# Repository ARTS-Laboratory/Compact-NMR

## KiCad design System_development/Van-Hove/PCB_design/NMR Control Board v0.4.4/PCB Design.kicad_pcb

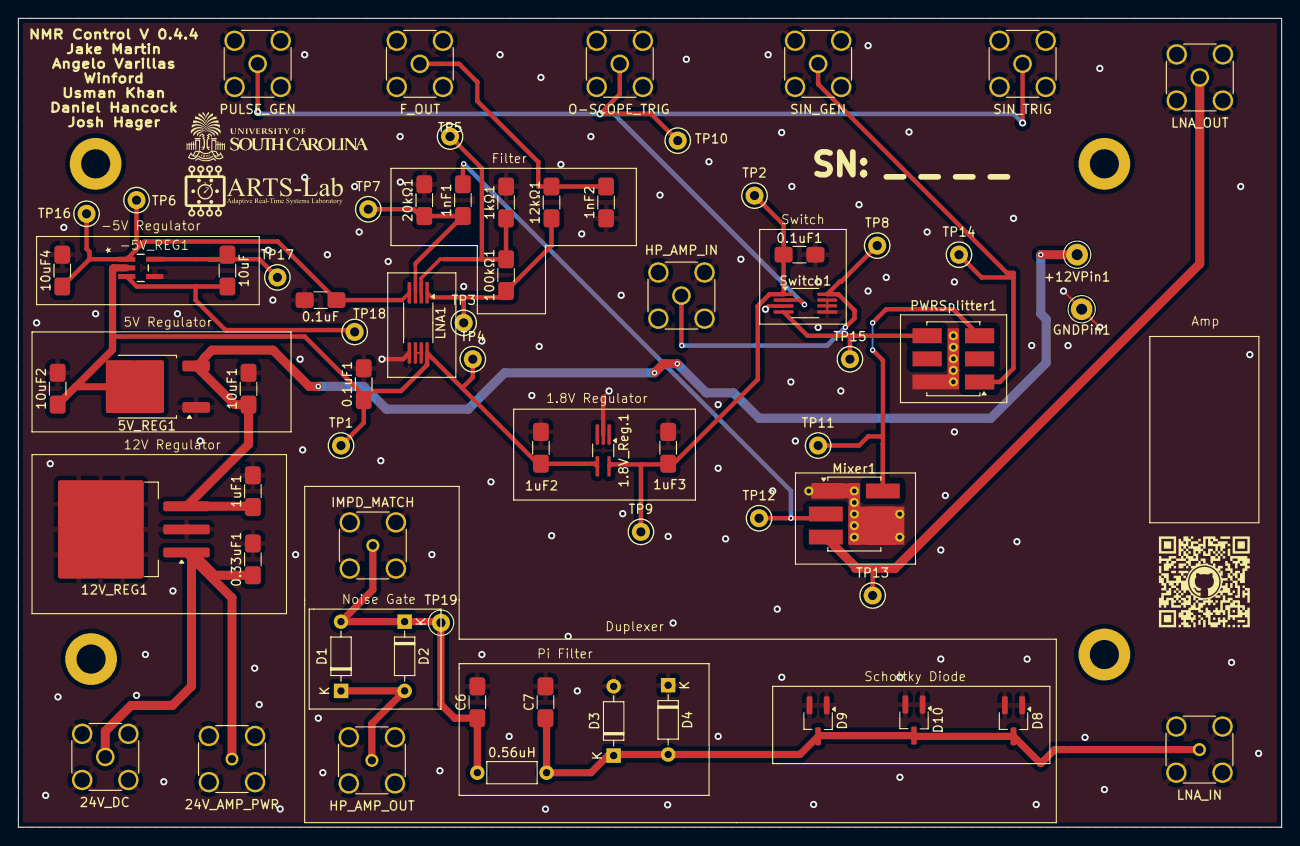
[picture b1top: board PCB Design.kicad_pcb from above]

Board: 2 copper layers, 139.0 x 89.0 mm, 68 parts (0 on the bottom side), 23 nets.

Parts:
0.1uF, 0.1uF1, 0.1uF1#2: 0.1μF; CustomR
0.33uF1: 0.33μF; CustomR
0.56uH: L; L_Axial_L5.3mm_D2.2mm_P7.62mm_Horizontal_Vishay_IM-1
1.8V_Reg.1: NCP715-1.8V; 1.8VReg
1kΩ1: 1kΩ; CustomR
1nF1, 1nF2: 1nF; CustomR
1uF1, 1uF2, 1uF3: 1μF; CustomR
5V_REG1: NCP1117-5.0_TO252; 5VReg2
10uF, 10uF1, 10uF2, 10uF4: 10μF; CustomR
12V_REG1: LM7812_TO220; 5VReg
12kΩ1: 12kΩ; CustomR
20kΩ1: 20kΩ; CustomR
24V_AMP_PWR: 24V Amp; SMA_Amphenol_132134-14_Vertical
24V_DC: 24V DC; SMA_Amphenol_132134_Vertical
100kΩ1: 100kΩ; CustomR
+12VPin1: Conn_Coaxial; Pin_D1.0mm_L10.0mm_LooseFit
-5V_REG1: LM828M5; Mf05A
C6: C14; CustomR
C7: C15; CustomR
D1, D2, D3, D4: 1N4148; D_DO-35_SOD27_P7.62mm_Horizontal
D8, D9, D10: D_Schottky_Dual_Series_AKC; TSOT-23_HandSoldering
F_OUT: Output Function; SMA_Amphenol_132134_Vertical
GNDPin1: Conn_Coaxial; Pin_D1.0mm_L10.0mm_LooseFit
HP_AMP_IN: Sine Out; SMA_Amphenol_132134_Vertical
HP_AMP_OUT: Input 1; SMA_Amphenol_132134-14_Vertical
IMPD_MATCH: Imped Match; SMA_Amphenol_132134-14_Vertical
LNA1: LM4565; LNA
LNA_IN: Output; SMA_Amphenol_132134-14_Vertical
LNA_OUT: Mix RF; SMA_Amphenol_132134_Vertical
Mixer1: ADE-6; Mixer2
O-SCOPE_TRIG: Trig Out; SMA_Amphenol_132134_Vertical
PULSE_GEN: Pulse Wave; SMA_Amphenol_132134_Vertical
PWRSplitter1: ADP-2-1W; Mini-Circuits_CD636_LandPatternPL-035
SIN_GEN: SPI In; SMA_Amphenol_132134_Vertical
SIN_TRIG: Sine Wave; SMA_Amphenol_132134_Vertical
Switch1: ADG901BRMZ; Switch
TP1, TP2, TP3, TP4, TP5, TP6, TP7, TP8, TP9, TP10, TP11, TP12, TP13, TP14, TP15, TP16, TP17, TP18, TP19: TestPoint; TestPoint_Keystone_5000-5004_Miniature

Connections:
GND: 0.1uF.2, 0.1uF1.2, 0.1uF1#2.2, 0.33uF1.2, 1.8V_Reg.1.2 (GND), 1kΩ1.2, 1nF2.1, 1uF1.2, 1uF2.2, 1uF3.2, 5V_REG1.1 (GND), 10uF1.2, 10uF2.2, 10uF4.2, 12V_REG1.2 (GND), 20kΩ1.2, 24V_AMP_PWR.2 (Ext), 24V_DC.2 (Ext), -5V_REG1.4 (GND), C6.2, C7.2, D3.2 (A), D4.1 (K), D8.1 (A), D8.2 (K), D9.1 (A), D9.2 (K), D10.1 (A), D10.2 (K), F_OUT.2 (Ext), GNDPin1.1 (In), HP_AMP_IN.2 (Ext), HP_AMP_OUT.2 (Ext), IMPD_MATCH.2 (Ext), LNA1.5 (+IN2), LNA_IN.2 (Ext), LNA_OUT.2 (Ext), Mixer1.1 (GND), Mixer1.4 (GND), Mixer1.5 (GND), O-SCOPE_TRIG.2 (Ext), PULSE_GEN.2 (Ext), PWRSplitter1.6 (GND), SIN_GEN.2 (Ext), SIN_TRIG.2 (Ext), Switch1.3 (GND), Switch1.5 (GND), Switch1.6 (GND), Switch1.7 (GND)
unnamed: 0.1uF1#2.1, 1.8V_Reg.1.5 (OUT), 1uF3.1, Switch1.1 (VDD), TP2.1, TP9.1
unnamed: 0.33uF1.1, 12V_REG1.1 (VI), 24V_AMP_PWR.1 (In), 24V_DC.1 (In)
unnamed: 1uF1.1, 5V_REG1.3 (VI), 10uF1.1, 12V_REG1.3 (VO), +12VPin1.1 (In)
unnamed: 10uF.1, -5V_REG1.5 (C1+), TP17.1
unnamed: 10uF.2, -5V_REG1.3 (C1-), TP18.1
unnamed: 0.1uF.1, 10uF4.1, -5V_REG1.1 (OUT), LNA1.4 (VEE), TP6.1, TP16.1
unnamed: 0.1uF1.1, 1.8V_Reg.1.4 (IN), 1uF2.1, 5V_REG1.2 (VO), 10uF2.1, -5V_REG1.2 (V+), LNA1.8 (VCC), TP1.1, TP4.1
unnamed: 0.56uH.1, C6.1, D1.2 (A), D2.1 (K), IMPD_MATCH.1 (In), TP19.1
unnamed: D1.1 (K), D2.2 (A), HP_AMP_OUT.1 (In)
unnamed: 0.56uH.2, C7.1, D3.1 (K), D4.2 (A), D8.3 (common), D9.3 (common), D10.3 (common), LNA_IN.1 (In)
unnamed: O-SCOPE_TRIG.1 (In), PULSE_GEN.1 (In), SIN_TRIG.1 (In), Switch1.2 (CTRL), TP10.1
unnamed: HP_AMP_IN.1 (In), Switch1.8 (RF2), TP8.1
unnamed: PWRSplitter1.1 (SUM), SIN_GEN.1 (In), TP14.1
unnamed: LNA_OUT.1 (In), Mixer1.3 (RF), TP13.1
unnamed: 1nF2.2, 12kΩ1.2, F_OUT.1 (In)
unnamed: 1nF1.1, 20kΩ1.1, LNA1.3 (+IN1), TP7.1
unnamed: 1kΩ1.1, 100kΩ1.2, LNA1.2 (-IN1), TP5.1
unnamed: LNA1.6 (-IN2), LNA1.7 (OUT2)
unnamed: 12kΩ1.1, 100kΩ1.1, LNA1.1 (OUT1), TP3.1
unnamed: 1nF1.2, Mixer1.2 (IF), TP12.1
unnamed: Mixer1.6 (LO), PWRSplitter1.3 (PORT1), TP11.1
unnamed: PWRSplitter1.4 (PORT2), Switch1.4 (RF1), TP15.1

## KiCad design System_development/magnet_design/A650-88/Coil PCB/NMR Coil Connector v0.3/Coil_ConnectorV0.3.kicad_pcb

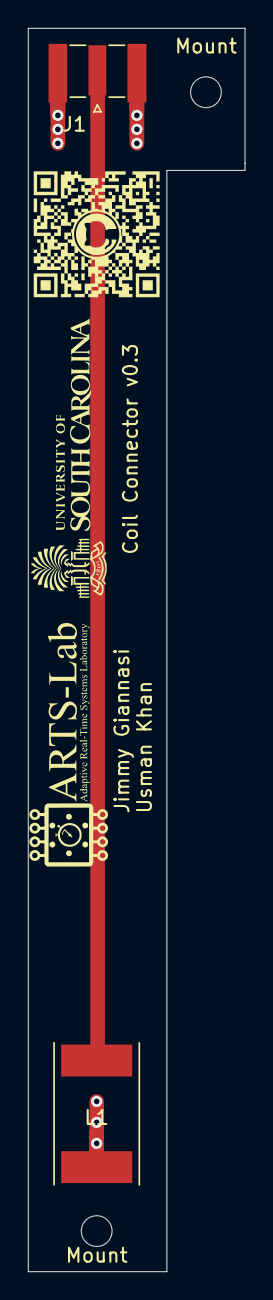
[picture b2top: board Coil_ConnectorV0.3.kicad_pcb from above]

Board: 2 copper layers, 15.5 x 88.9 mm, 4 parts (0 on the bottom side), 2 nets.

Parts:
J1: Conn_Coaxial; SMA_Samtec_SMA-J-P-X-ST-EM1_EdgeMount
L1: L; L_Coil
Mount: MountingHole_2.2mm_M2
Mount#2: MountingHole_2.2mm_M2

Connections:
GND: J1.2, L1.2
unnamed: J1.1, L1.1

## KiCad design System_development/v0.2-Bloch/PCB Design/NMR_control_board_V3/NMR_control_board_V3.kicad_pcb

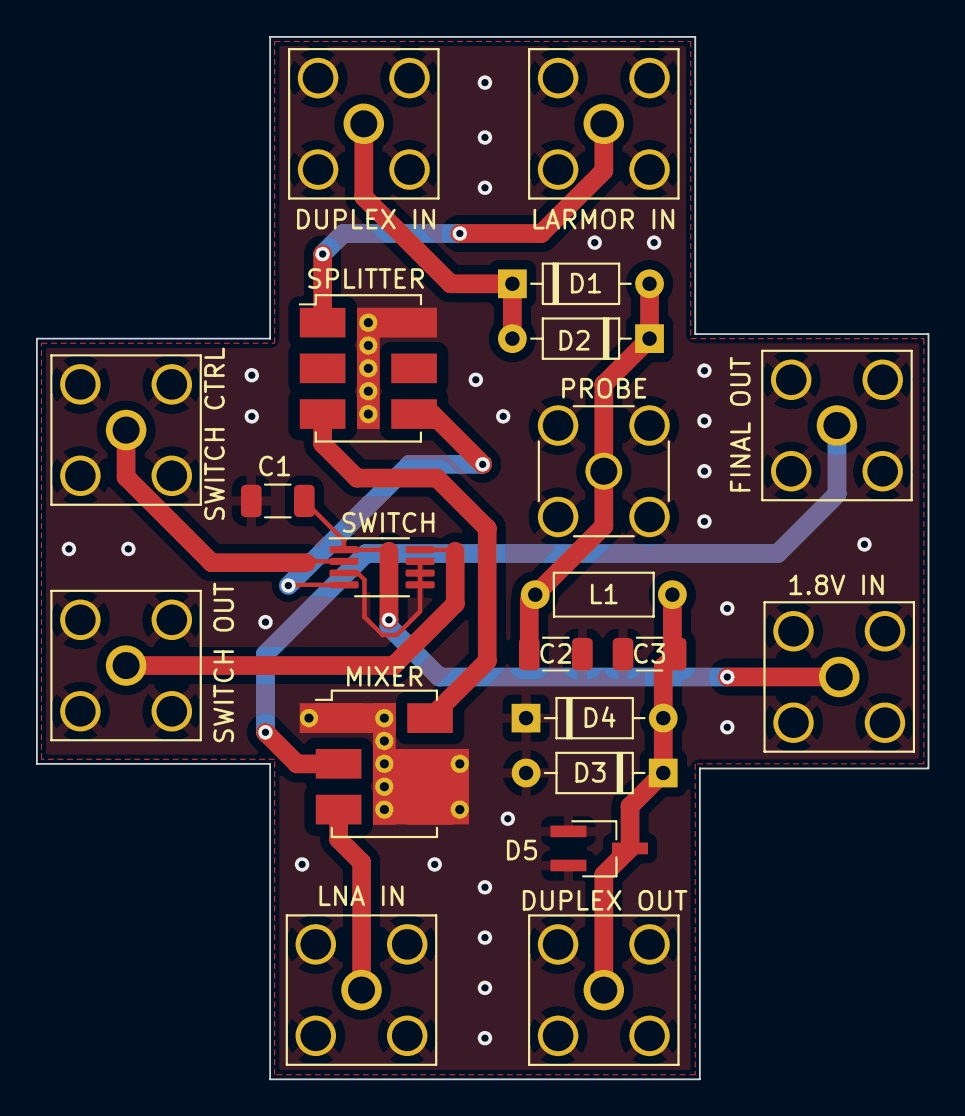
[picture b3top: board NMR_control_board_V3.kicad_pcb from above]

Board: 2 copper layers, 49.5 x 57.9 mm, 21 parts (0 on the bottom side), 12 nets.

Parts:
1.8V IN: Conn_Coaxial; SMA_Amphenol_132203-12_Horizontal
C1: 0.1 uF; C_1206_3216Metric
C2, C3: C; C_1206_3216Metric
D1, D2, D3, D4: 1N4148; D_DO-35_SOD27_P7.62mm_Horizontal
D5: D_Schottky_Dual_Series_AKC; TSOT-23_HandSoldering
DUPLEX IN: Conn_Coaxial; SMA_Amphenol_132203-12_Horizontal
DUPLEX OUT: Conn_Coaxial; SMA_Amphenol_132203-12_Horizontal
FINAL OUT: Conn_Coaxial; SMA_Amphenol_132203-12_Horizontal
L1: INDUCTOR; L_Axial_L5.3mm_D2.2mm_P7.62mm_Horizontal_Vishay_IM-1
LARMOR IN: Conn_Coaxial; SMA_Amphenol_132203-12_Horizontal
LNA IN: Conn_Coaxial; SMA_Amphenol_132203-12_Horizontal
MIXER: ADE-6; Mini-Circuits_CD542_LandPatternPL-052
PROBE: Conn_Coaxial; SMA_Amphenol_132291-12_Vertical
SPLITTER: ADP-2-1W; Mini-Circuits_CD636_LandPatternPL-035
SWITCH: ADG901BRMZ; MSOP-8_3x3mm_P0.65mm
SWITCH CTRL: Conn_Coaxial; SMA_Amphenol_132203-12_Horizontal
SWITCH OUT: Conn_Coaxial; SMA_Amphenol_132203-12_Horizontal

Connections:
GND: 1.8V IN.2 (Ext), C1.1, C2.2, C3.2, D3.2 (A), D4.1 (K), D5.1 (A), D5.2 (K), DUPLEX IN.2 (Ext), DUPLEX OUT.2 (Ext), FINAL OUT.2 (Ext), LARMOR IN.2 (Ext), LNA IN.2 (Ext), MIXER.1 (GND), MIXER.4 (GND), MIXER.5 (GND), PROBE.2 (Ext), SPLITTER.6 (GND), SWITCH.3 (GND), SWITCH.5 (GND), SWITCH.6 (GND), SWITCH.7 (GND), SWITCH CTRL.2 (Ext), SWITCH OUT.2 (Ext)
unnamed: 1.8V IN.1 (In), C1.2, SWITCH.1 (VDD)
unnamed: C2.1, D1.2 (A), D2.1 (K), L1.1, PROBE.1 (In)
unnamed: C3.1, D3.1 (K), D4.2 (A), D5.3 (common), DUPLEX OUT.1 (In), L1.2
unnamed: D1.1 (K), D2.2 (A), DUPLEX IN.1 (In)
unnamed: LARMOR IN.1 (In), SPLITTER.1 (SUM)
unnamed: SWITCH.2 (CTRL), SWITCH CTRL.1 (In)
unnamed: LNA IN.1 (In), MIXER.3 (RF)
unnamed: FINAL OUT.1 (In), MIXER.2 (IF)
unnamed: SWITCH.8 (RF2), SWITCH OUT.1 (In)
unnamed: MIXER.6 (LO), SPLITTER.3 (PORT1)
unnamed: SPLITTER.4 (PORT2), SWITCH.4 (RF1)

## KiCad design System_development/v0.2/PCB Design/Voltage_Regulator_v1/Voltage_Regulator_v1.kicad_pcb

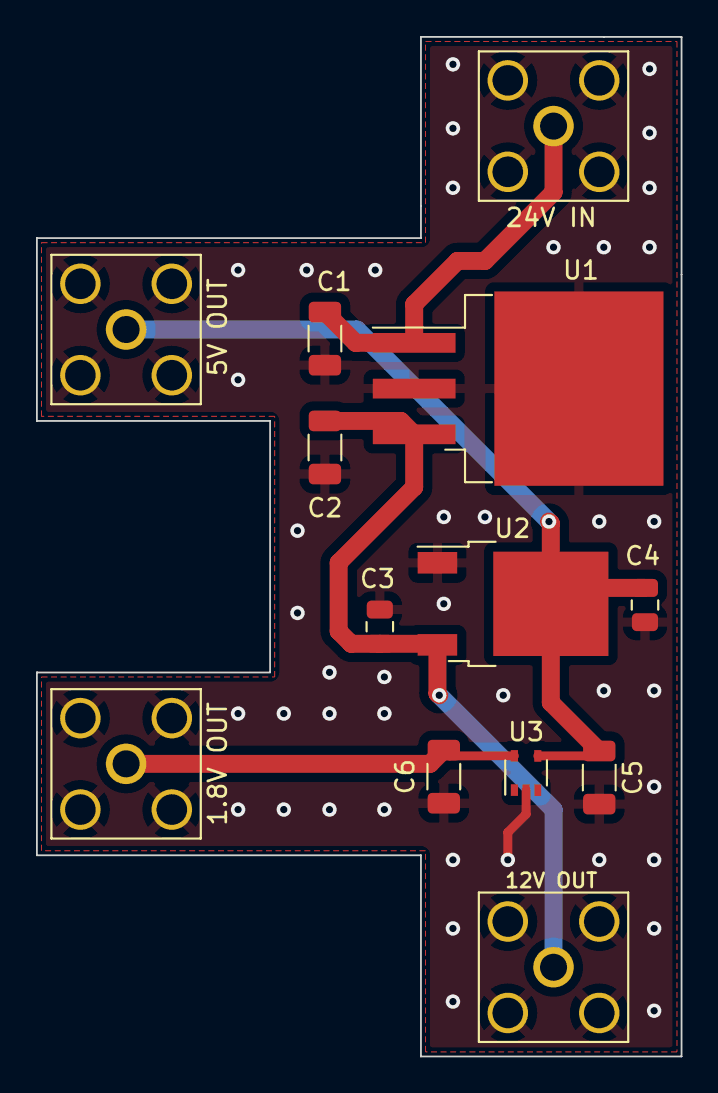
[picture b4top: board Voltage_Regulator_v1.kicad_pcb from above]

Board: 2 copper layers, 35.8 x 56.6 mm, 13 parts (0 on the bottom side), 5 nets.

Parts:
1.8V OUT, 5V OUT, 12V OUT, 24V IN: Conn_Coaxial; SMA_Amphenol_132203-12_Horizontal
C1: 0.33 uF; C_1206_3216Metric
C2, C5, C6: 1 uF; C_1206_3216Metric
C3, C4: 10 uF; C_0805_2012Metric
U1: LM7812_TO220; TO-263-3_TabPin2
U2: NCP1117-5.0_TO252; TO-252-2
U3: NCP715-1.8V; SOT-353_SC-70-5

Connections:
GND: 1.8V OUT.2 (Ext), 5V OUT.2 (Ext), 12V OUT.2 (Ext), 24V IN.2 (Ext), C1.2, C2.2, C3.2, C4.2, C5.2, C6.2, U1.2 (GND), U2.1 (GND), U3.2 (GND)
unnamed: 24V IN.1 (In), C1.1, U1.1 (VI)
unnamed: 12V OUT.1 (In), C2.1, C3.1, U1.3 (VO), U2.3 (VI)
unnamed: 5V OUT.1 (In), C4.1, C5.1, U2.2 (VO), U3.4 (IN)
unnamed: 1.8V OUT.1 (In), C6.1, U3.5 (OUT)

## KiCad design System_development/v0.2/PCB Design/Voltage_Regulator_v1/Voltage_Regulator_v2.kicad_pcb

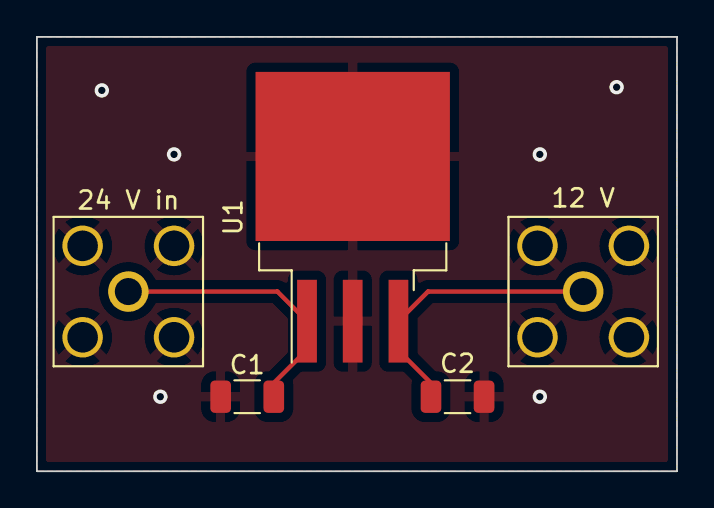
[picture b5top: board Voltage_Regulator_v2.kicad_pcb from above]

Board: 2 copper layers, 35.6 x 24.1 mm, 5 parts (0 on the bottom side), 3 nets.

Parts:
12 V, 24 V in: Conn_Coaxial; SMA_Amphenol_132203-12_Horizontal
C1: 0.33 uF; C_1206_3216Metric
C2: 1 uF; C_1206_3216Metric
U1: LM7812_TO220; TO-263-3_TabPin2

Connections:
GND: 12 V.2 (Ext), 24 V in.2 (Ext), C1.2, C2.2, U1.2 (GND)
unnamed: 24 V in.1 (In), C1.1, U1.1 (VI)
unnamed: 12 V.1 (In), C2.1, U1.3 (VO)

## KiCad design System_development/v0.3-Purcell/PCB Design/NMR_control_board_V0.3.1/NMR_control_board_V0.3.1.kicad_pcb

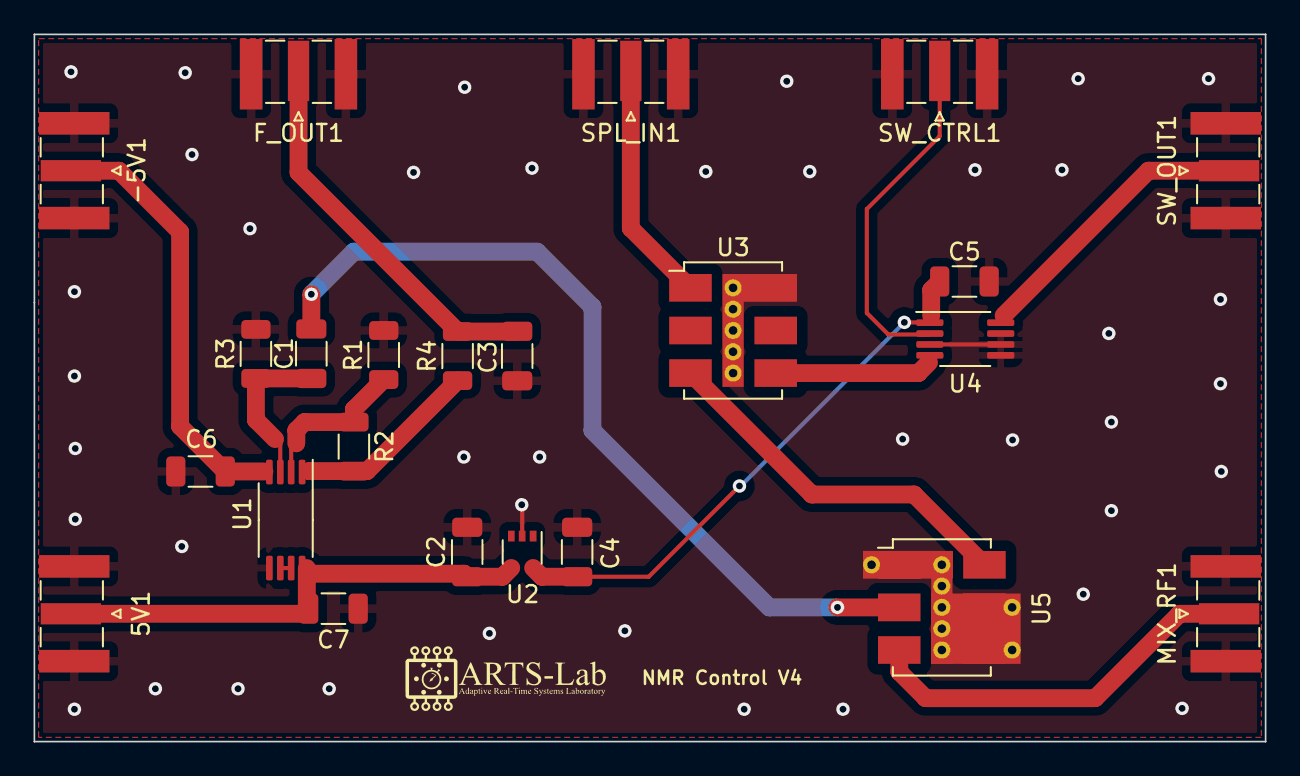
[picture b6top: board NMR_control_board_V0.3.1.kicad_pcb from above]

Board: 2 copper layers, 73.4 x 42.2 mm, 23 parts (0 on the bottom side), 16 nets.

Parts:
5V1: Conn_Coaxial; SMA_Samtec_SMA-J-P-X-ST-EM1_EdgeMount
-5V1: Conn_Coaxial; SMA_Samtec_SMA-J-P-X-ST-EM1_EdgeMount
C1, C3: C; C_1206_3216Metric
C2, C4: 1 uF; C_1206_3216Metric
C5: 0.1 uF; C_1206_3216Metric
C6, C7: 0.1uF; C_1206_3216Metric
F_OUT1: Conn_Coaxial; SMA_Samtec_SMA-J-P-X-ST-EM1_EdgeMount
MIX_RF1: Conn_Coaxial; SMA_Samtec_SMA-J-P-X-ST-EM1_EdgeMount
R1, R2, R3, R4: R; R_1206_3216Metric
SPL_IN1: Conn_Coaxial; SMA_Samtec_SMA-J-P-X-ST-EM1_EdgeMount
SW_CTRL1: Conn_Coaxial; SMA_Samtec_SMA-J-P-X-ST-EM1_EdgeMount
SW_OUT1: Conn_Coaxial; SMA_Samtec_SMA-J-P-X-ST-EM1_EdgeMount
U1: LM4565; TSSOP-8_4.4x3mm_P0.65mm
U2: NCP715-1.8V; SOT-353_SC-70-5
U3: ADP-2-1W; Mini-Circuits_CD636_LandPatternPL-035
U4: ADG901BRMZ; MSOP-8_3x3mm_P0.65mm
U5: ADE-6; Mini-Circuits_CD542_LandPatternPL-052

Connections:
GND: 5V1.2 (Ext), -5V1.2 (Ext), C2.2, C3.1, C4.2, C5.1, C6.1, C7.1, F_OUT1.2 (Ext), MIX_RF1.2 (Ext), R1.1, R3.2, SPL_IN1.2 (Ext), SW_CTRL1.2 (Ext), SW_OUT1.2 (Ext), U1.5 (+IN2), U2.2 (GND), U3.6 (GND), U4.3 (GND), U4.5 (GND), U4.6 (GND), U4.7 (GND), U5.1 (GND), U5.4 (GND), U5.5 (GND)
unnamed: -5V1.1 (In), C6.2, U1.4 (VEE)
unnamed: C1.1, R3.1, U1.3 (+IN1)
unnamed: C1.2, U5.2 (IF)
unnamed: 5V1.1 (In), C2.1, C7.2, U1.8 (VCC), U2.4 (IN)
unnamed: C3.2, F_OUT1.1 (In), R4.2
unnamed: C4.1, C5.2, U2.5 (OUT), U4.1 (VDD)
unnamed: MIX_RF1.1 (In), U5.3 (RF)
unnamed: R1.2, R2.1, U1.2 (-IN1)
unnamed: R2.2, R4.1, U1.1 (OUT1)
unnamed: SPL_IN1.1 (In), U3.1 (SUM)
unnamed: SW_CTRL1.1 (In), U4.2 (CTRL)
unnamed: SW_OUT1.1 (In), U4.8 (RF2)
unnamed: U1.6 (-IN2), U1.7 (OUT2)
unnamed: U3.3 (PORT1), U5.6 (LO)
unnamed: U3.4 (PORT2), U4.4 (RF1)

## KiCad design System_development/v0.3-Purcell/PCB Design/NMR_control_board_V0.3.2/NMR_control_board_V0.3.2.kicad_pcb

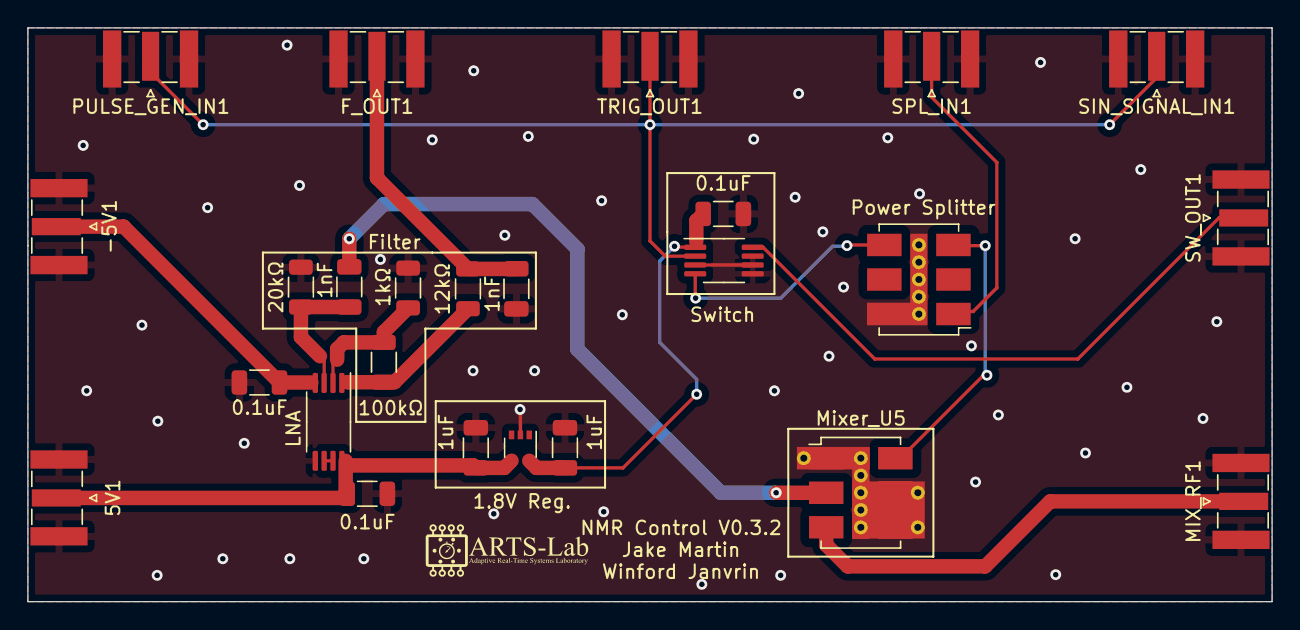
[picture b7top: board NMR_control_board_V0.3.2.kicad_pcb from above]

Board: 2 copper layers, 91.4 x 42.2 mm, 25 parts (0 on the bottom side), 16 nets.

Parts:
1.8V Reg.: NCP715-1.8V; SOT-353_SC-70-5
1kΩ, 12kΩ, 20kΩ, 100kΩ: R; R_1206_3216Metric
1nF, 1nF#2: C; C_1206_3216Metric
5V1: Conn_Coaxial; SMA_Samtec_SMA-J-P-X-ST-EM1_EdgeMount
-5V1: Conn_Coaxial; SMA_Samtec_SMA-J-P-X-ST-EM1_EdgeMount
C2, C4: 1uF; C_1206_3216Metric
C5, C6, C7: 0.1uF; C_1206_3216Metric
F_OUT1: Conn_Coaxial; SMA_Samtec_SMA-J-P-X-ST-EM1_EdgeMount
LNA: LM4565; TSSOP-8_4.4x3mm_P0.65mm
MIX_RF1: Conn_Coaxial; SMA_Samtec_SMA-J-P-X-ST-EM1_EdgeMount
Mixer_U5: ADE-6; Mini-Circuits_CD542_LandPatternPL-052
PULSE_GEN_IN1: Conn_Coaxial; SMA_Samtec_SMA-J-P-X-ST-EM1_EdgeMount
Power Splitter: ADP-2-1W; Mini-Circuits_CD636_LandPatternPL-035
SIN_SIGNAL_IN1: Conn_Coaxial; SMA_Samtec_SMA-J-P-X-ST-EM1_EdgeMount
SPL_IN1: Conn_Coaxial; SMA_Samtec_SMA-J-P-X-ST-EM1_EdgeMount
SW_OUT1: Conn_Coaxial; SMA_Samtec_SMA-J-P-X-ST-EM1_EdgeMount
Switch: ADG901BRMZ; MSOP-8_3x3mm_P0.65mm
TRIG_OUT1: Conn_Coaxial; SMA_Samtec_SMA-J-P-X-ST-EM1_EdgeMount

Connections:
GND: 1.8V Reg..2 (GND), 1kΩ.1, 1nF#2.1, 5V1.2 (Ext), 20kΩ.2, -5V1.2 (Ext), C2.2, C4.2, C5.1, C6.1, C7.1, F_OUT1.2 (Ext), LNA.5 (+IN2), MIX_RF1.2 (Ext), Mixer_U5.1 (GND), Mixer_U5.4 (GND), Mixer_U5.5 (GND), PULSE_GEN_IN1.2 (Ext), Power Splitter.6 (GND), SIN_SIGNAL_IN1.2 (Ext), SPL_IN1.2 (Ext), SW_OUT1.2 (Ext), Switch.3 (GND), Switch.5 (GND), Switch.6 (GND), Switch.7 (GND), TRIG_OUT1.2 (Ext)
unnamed: 1.8V Reg..4 (IN), 5V1.1 (In), C2.1, C7.2, LNA.8 (VCC)
unnamed: -5V1.1 (In), C6.2, LNA.4 (VEE)
unnamed: 1nF.1, 20kΩ.1, LNA.3 (+IN1)
unnamed: 1nF.2, Mixer_U5.2 (IF)
unnamed: 1nF#2.2, 12kΩ.2, F_OUT1.1 (In)
unnamed: 1.8V Reg..5 (OUT), C4.1, C5.2, Switch.1 (VDD)
unnamed: MIX_RF1.1 (In), Mixer_U5.3 (RF)
unnamed: 1kΩ.2, 100kΩ.1, LNA.2 (-IN1)
unnamed: 12kΩ.1, 100kΩ.2, LNA.1 (OUT1)
unnamed: Power Splitter.1 (SUM), SPL_IN1.1 (In)
unnamed: SW_OUT1.1 (In), Switch.8 (RF2)
unnamed: LNA.6 (-IN2), LNA.7 (OUT2)
unnamed: Mixer_U5.6 (LO), Power Splitter.3 (PORT1)
unnamed: Power Splitter.4 (PORT2), Switch.4 (RF1)
unnamed: PULSE_GEN_IN1.1 (In), SIN_SIGNAL_IN1.1 (In), Switch.2 (CTRL), TRIG_OUT1.1 (In)
